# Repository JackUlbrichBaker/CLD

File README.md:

### Welcome to the Can LED Driver Git repo!

This is an STM32 based smart load switch that is capable of driving up to 60A at 20V (ignoring thermals)
Currently it is just a hardware repo - software TBC.  I know it is overkill but that is more fun than simplicity :seal:
<details open>
<summary>PCB: </summary>

</details>

<details open>
<summary>Schematic: </summary>

</details>

- [x] Hardware schematic
- [x] PCB layed out 
- [ ] PCB routed
- [ ] PCB ordered and populated
- [ ] Software written
- [ ] software tested

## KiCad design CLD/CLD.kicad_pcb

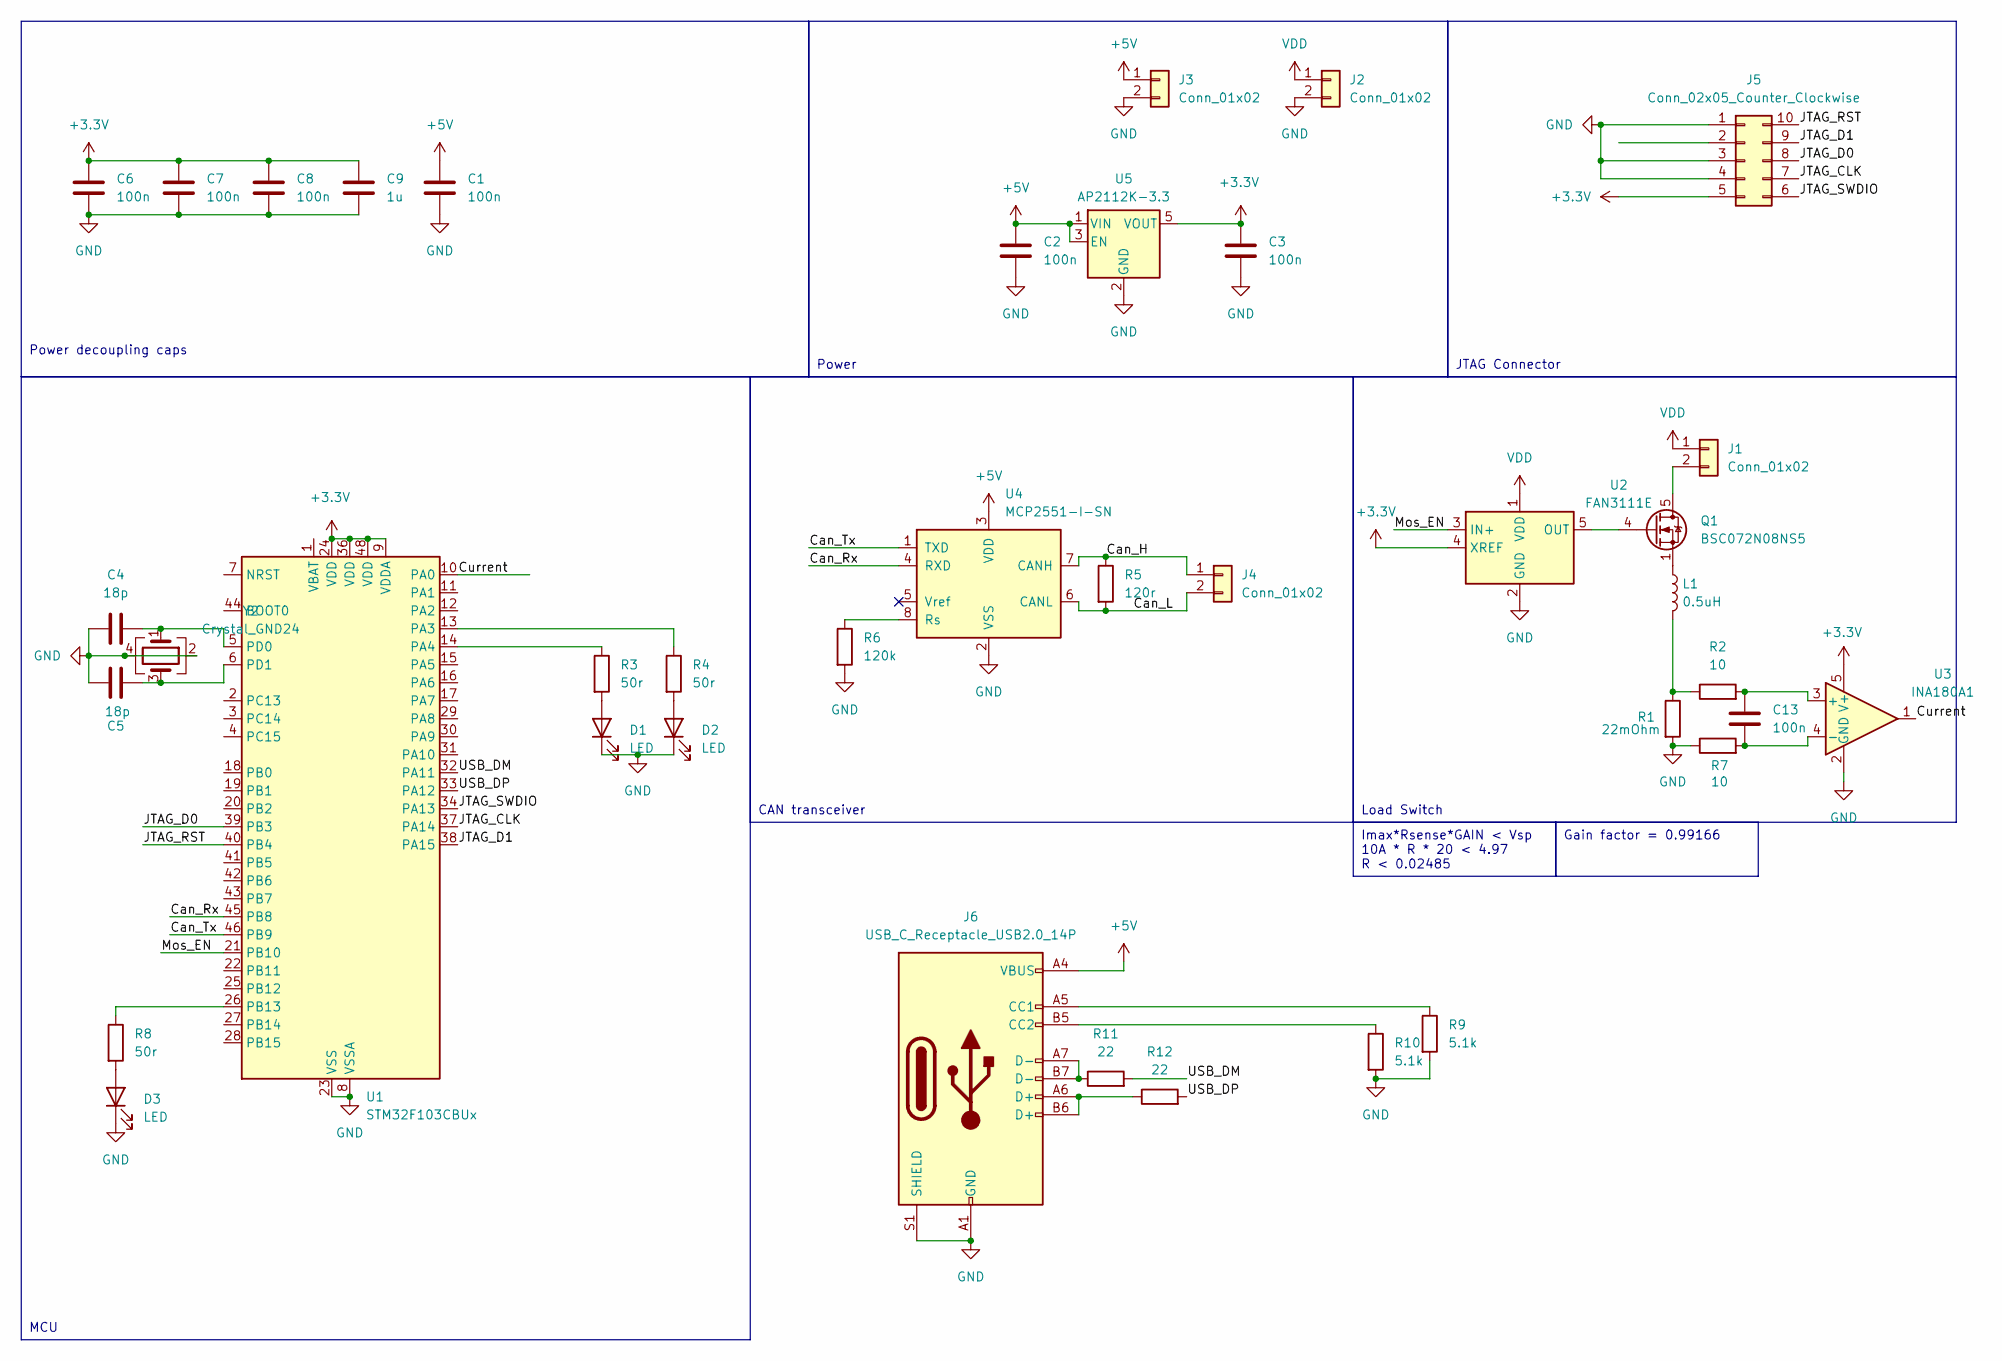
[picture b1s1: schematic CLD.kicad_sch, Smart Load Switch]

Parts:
C1, C2, C3, C6, C7, C8, C13: 100n; C_0603_1608Metric
C4, C5: 18p; C_0603_1608Metric
C9: 1u; C_0603_1608Metric
D1, D2, D3: LED; D_0603_1608Metric
J1, J2, J3, J4: Conn_01x02; PinHeader_1x02_P2.54mm_Vertical
J5: Conn_02x05_Counter_Clockwise; PinHeader_2x05_P1.27mm_Vertical_SMD
J6: USB_C_Receptacle_USB2.0_14P; USB_C_Receptacle_GCT_USB4105-xx-A_16P_TopMnt_Horizontal
L1: 0.5uH; L_Bourns-SRN8040_8x8.15mm
Q1: BSC072N08NS5; TDSON-8-1
R1: 22mOhm; R_1206_3216Metric
R2, R7: 10; R_0603_1608Metric
R3, R4, R8: 50r; R_0603_1608Metric
R5: 120r; R_0603_1608Metric
R6: 120k; R_0603_1608Metric
R9, R10: 5.1k; R_0603_1608Metric
R11, R12: 22; R_0603_1608Metric
U1: STM32F103CBUx; QFN-48-1EP_7x7mm_P0.5mm_EP5.6x5.6mm
U2: FAN3111E; SOT-23-5
U3: INA180A1; SOT-23-5
U4: MCP2551-I-SN; SOIC-8_3.9x4.9mm_P1.27mm
U5: AP2112K-3.3; SOT-23-5
Y2: Crystal_GND24; Crystal_SMD_Abracon_ABM3C-4Pin_5.0x3.2mm

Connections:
+3.3V: C3.1, C6.1, C7.1, C8.1, C9.1, J5.5, U1.9 (VDDA), U1.24 (VDD), U1.36 (VDD), U1.48 (VDD), U2.4 (XREF), U3.5 (V+), U5.5 (VOUT)
+5V: C1.1, C2.1, J3.1, J6.A4 (VBUS), J6.A9 (VBUS), J6.B4 (VBUS), J6.B9 (VBUS), U4.3 (VDD), U5.1 (VIN), U5.3 (EN); also elsewhere on the board
/Can_H: J4.1, R5.1, U4.7 (CANH)
/Can_L: J4.2, R5.2, U4.6 (CANL)
/Can_Rx: U1.45 (PB8), U4.4 (RXD)
/Can_Tx: U1.46 (PB9), U4.1 (TXD)
/Current: U1.10 (PA0), U3.1
/JTAG_CLK: J5.7, U1.37 (PA14)
/JTAG_D0: J5.8, U1.39 (PB3)
/JTAG_D1: J5.9, U1.38 (PA15)
/JTAG_RST: J5.10, U1.40 (PB4)
/JTAG_SWDIO: J5.6, U1.34 (PA13)
/Mos_EN: U1.21 (PB10), U2.3 (IN+)
/USB_DM: R11.2, U1.32 (PA11)
/USB_DP: R12.2, U1.33 (PA12)
GND: C1.2, C2.2, C3.2, C4.1, C5.1, C6.2, C7.2, C8.2, C9.2, D1.1 (K), D2.1 (K), D3.1 (K), J2.2, J3.2, J5.1, J5.3, J5.4, J6.A1 (GND), J6.A12 (GND), J6.B1 (GND), J6.B12 (GND), J6.S1 (SHIELD), R1.2, R6.2, R7.1, R9.2, R10.2, U1.8 (VSSA), U1.23 (VSS), U1.35 (VSS), U1.47 (VSS), U1.49 (VSS), U2.2 (GND), U3.2 (GND), U4.2 (VSS), U5.2 (GND), Y2.2, Y2.4; also elsewhere on the board
unnamed: D1.2 (A), R3.2
unnamed: D2.2 (A), R4.2
unnamed: D3.2 (A), R8.2
unnamed: J1.2, Q1.5 (D)
unnamed: J6.A5 (CC1), R9.1
unnamed: J6.B5 (CC2), R10.1
unnamed: J6.A6 (D+), J6.B6 (D+), R12.1
unnamed: J6.A7 (D-), J6.B7 (D-), R11.1
unnamed: L1.1, Q1.1 (S), Q1.2 (S), Q1.3 (S)
unnamed: L1.2, R1.1, R2.1
unnamed: Q1.4 (G), U2.5 (OUT)
unnamed: R4.1, U1.13 (PA3)
unnamed: R3.1, U1.14 (PA4)
unnamed: R8.1, U1.26 (PB13)
unnamed: C4.2, U1.5 (PD0), Y2.1
unnamed: C5.2, U1.6 (PD1), Y2.3
unnamed: C13.1, R2.2, U3.3 (+)
unnamed: C13.2, R7.2, U3.4 (-)
unnamed: R6.1, U4.8 (Rs)
VDD: J1.1, J2.1, U2.1 (VDD)

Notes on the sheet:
Imax*Rsense*GAIN < Vsp 10A * R * 20 < 4.97 R < 0.02485
Power
JTAG Connector
Load Switch
MCU
Power decoupling caps
Gain factor = 0.99166
CAN transceiver

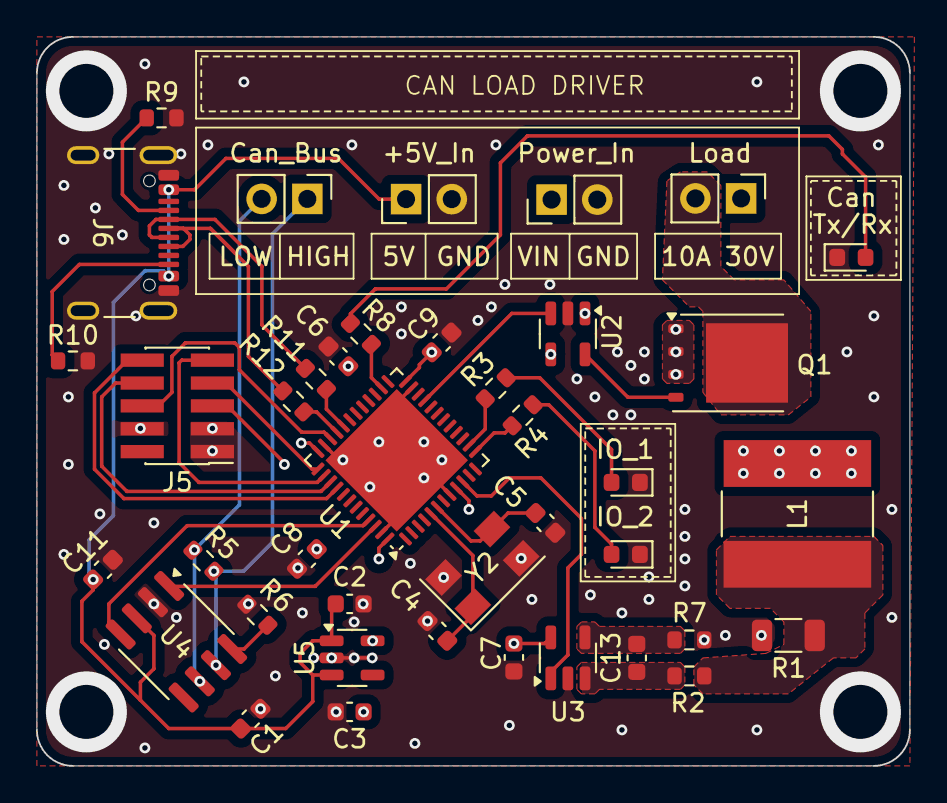
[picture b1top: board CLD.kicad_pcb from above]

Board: 4 copper layers, 48.5 x 40.5 mm, 40 parts (0 on the bottom side), 36 nets.

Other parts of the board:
C11: 100n; C_0603_1608Metric

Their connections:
+5V: C11.1; also elsewhere on the board
GND: C11.2; also elsewhere on the board

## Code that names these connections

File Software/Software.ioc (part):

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Mcu.Name=STM32F103CBUx
Mcu.Package=UFQFPN48
Mcu.UserName=STM32F103CBUx
PA0-WKUP.GPIOParameters=GPIO_Label
PA0-WKUP.GPIO_Label=CURR_IN
PA0-WKUP.Signal=ADCx_IN0
PA11.Mode=Device
PA11.Signal=USB_DM
PA12.Mode=Device
PA12.Signal=USB_DP
PA13.Mode=JTAG_5_pins
PA13.Signal=SYS_JTMS-SWDIO
PA14.Mode=JTAG_5_pins
PA14.Signal=SYS_JTCK-SWCLK
PA15.Mode=JTAG_5_pins
PA15.Signal=SYS_JTDI
PB10.Signal=S_TIM2_CH3
PB3.Mode=JTAG_5_pins
PB3.Signal=SYS_JTDO-TRACESWO
PB4.Mode=JTAG_5_pins
PB4.Signal=SYS_NJTRST
PB8.Mode=CAN_Activate
PB8.Signal=CAN_RX
PB9.Mode=CAN_Activate
PB9.Signal=CAN_TX
PD0-OSC_IN.Mode=HSE-External-Oscillator
PD0-OSC_IN.Signal=RCC_OSC_IN
PD1-OSC_OUT.Mode=HSE-External-Oscillator
PD1-OSC_OUT.Signal=RCC_OSC_OUT
RCC.SYSCLKFreq_VALUE=48000000
RCC.SYSCLKSource=RCC_SYSCLKSOURCE_PLLCLK
board=custom

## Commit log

2024-05-10 added README
2024-05-10 test feature:
2024-05-17 update 17/09
2024-05-20 howdy
2024-05-20 gitignore
2024-05-20 commmit schem v1.0
2024-06-08 PCB routed
2024-06-11 add USB + crystal
2024-06-13 generated gerbers
2024-06-24 added USB serial resistors oops
